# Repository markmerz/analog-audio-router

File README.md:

# analog-audio-router
Schematics and firmware for analog line level audio router/switchbox.

When You have some number of older audio gear then inputs count of power amplifier comes an issue. 
It would be nice to have some kind of switchbox for RCA inputs. There is not something like that in
the market, so i'm building one by myself. With blackjack!

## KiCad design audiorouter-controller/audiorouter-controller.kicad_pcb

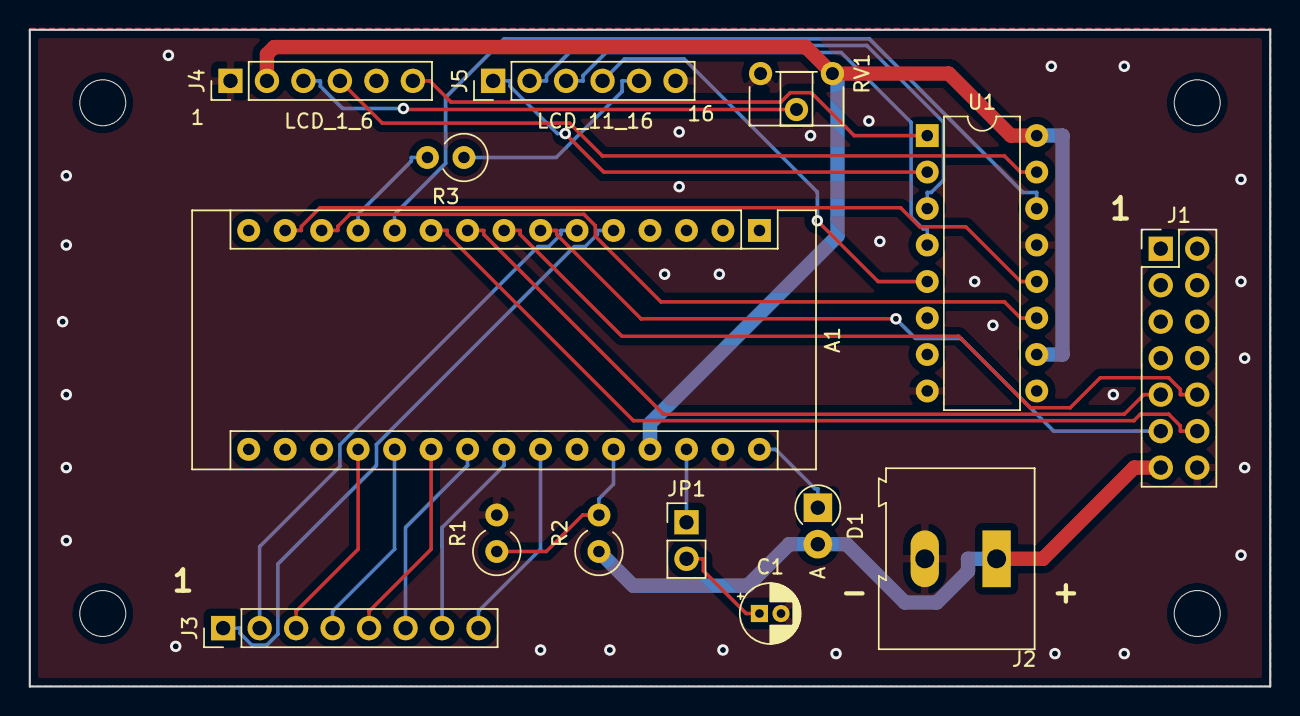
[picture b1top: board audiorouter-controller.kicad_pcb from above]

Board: 2 copper layers, 86.4 x 45.7 mm, 18 parts (0 on the bottom side), 31 nets.

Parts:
A1: Arduino_Nano_v3.x; Arduino_Nano
C1: 10u; CP_Radial_D4.0mm_P1.50mm
D1: N4007; D_T-1_P2.54mm_Vertical_AnodeUp
H1, H2, H3, H4: MountingHole; MountingHole_3.2mm_M3
J1: ToBoards; PinHeader_2x07_P2.54mm_Vertical
J2: PowerIn; TerminalBlock_Altech_AK300-2_P5.00mm
J3: AUX; PinHeader_1x08_P2.54mm_Vertical
J4: LCD_1_6; PinHeader_1x06_P2.54mm_Vertical
J5: LCD_11_16; PinHeader_1x06_P2.54mm_Vertical
JP1: progEnable; PinHeader_1x02_P2.54mm_Vertical
R1: 33k; R_Axial_DIN0309_L9.0mm_D3.2mm_P2.54mm_Vertical
R2: 47k; R_Axial_DIN0309_L9.0mm_D3.2mm_P2.54mm_Vertical
R3: 220; R_Axial_DIN0309_L9.0mm_D3.2mm_P2.54mm_Vertical
RV1: 10k; Potentiometer_ACP_CA6-H2,5_Horizontal
U1: 74HC595; DIP-16_W7.62mm

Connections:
+5V: A1.27, J4.2, RV1.1, U1.10, U1.16
AUX1: A1.5, J3.1
AUX2: A1.6, J3.2
AUX3: A1.19, J3.3
AUX4: A1.20, J3.4
AUX5: A1.21, J3.5
AUX6: A1.22, J3.6
AUX7: A1.23, J3.7
AUX8: A1.24, J3.8
GND: A1.29, C1.2, J1.14, J2.2, J4.1, J4.5, J5.6, R1.2, RV1.3, U1.8, U1.13
LCD_LED: A1.12, R3.2
LCD_RClock: A1.14, U1.12
LCD_SerialClock: A1.13, U1.11
LCD_SerialOut: A1.11, U1.14
unnamed: A1.28, JP1.1
unnamed: A1.30, D1.1
unnamed: C1.1, JP1.2
unnamed: J4.3, RV1.2
unnamed: J4.4, U1.15
unnamed: J4.6, U1.1
unnamed: J5.1, U1.2
unnamed: J5.2, U1.3
unnamed: J5.3, U1.4
unnamed: J5.4, U1.5
unnamed: J5.5, R3.1
OutputEnable: A1.10, J1.12
PowerIn: D1.2, J1.13, J2.1, R2.1
PowerMeasure: A1.26, R1.1, R2.2
RClock: A1.8, J1.10
SerialClock: A1.7, J1.11
SerialOut: A1.9, J1.9

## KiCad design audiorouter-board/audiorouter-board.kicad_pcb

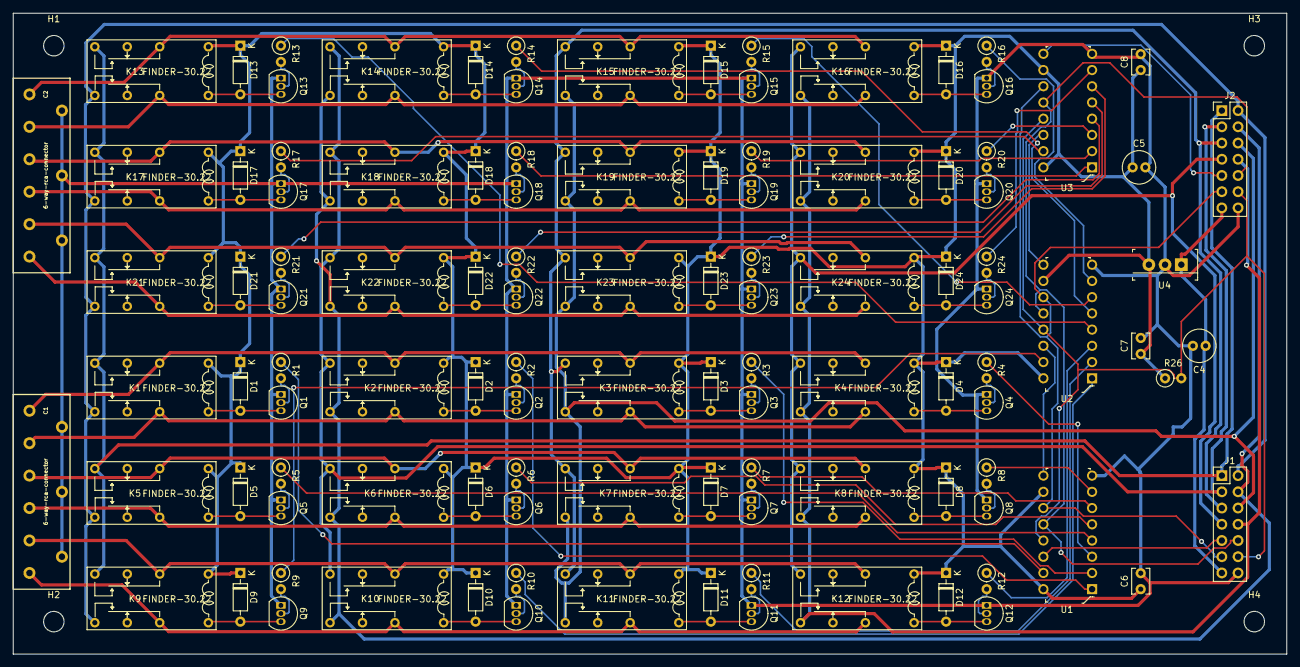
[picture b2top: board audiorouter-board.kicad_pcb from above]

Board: 2 copper layers, 199.4 x 100.3 mm, 114 parts (0 on the bottom side), 102 nets.

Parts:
C1, C2: 6-way-rca-connector; 6-way-rca-connector-on-edge
C4, C5: 10u; C_Radial_D5.0mm_H11.0mm_P2.00mm
C6, C7, C8: 10n; C_Disc_D3.8mm_W2.6mm_P2.50mm
D1, D2, D3, D4, D5, D6, D7, D8, D9, D10, D11, D12, D13, D14, D15, D16, D17, D18, D19, D20, D21, D22, D23, D24: 1N914; D_DO-35_SOD27_P7.62mm_Horizontal
H1, H2, H3, H4: MountingHole; MountingHole_3.2mm_M3
J1: Input_Ribbon_Connector; PinHeader_2x07_P2.54mm_Vertical
J2: Output_Ribbon_Connector; PinHeader_2x07_P2.54mm_Vertical
K1, K2, K3, K4, K5, K6, K7, K8, K9, K10, K11, K12, K13, K14, K15, K16, K17, K18, K19, K20, K21, K22, K23, K24: FINDER-30.22; RY12w-k_bigger_holes
Q1, Q2, Q3, Q4, Q5, Q6, Q7, Q8, Q9, Q10, Q11, Q12, Q13, Q14, Q15, Q16, Q17, Q18, Q19, Q20, Q21, Q22, Q23, Q24: PN2222A; TO-92_Inline
R1, R2, R3, R4, R5, R6, R7, R8, R9, R10, R11, R12, R13, R14, R15, R16, R17, R18, R19, R20, R21, R22, R23, R24: 1k; R_Axial_DIN0207_L6.3mm_D2.5mm_P2.54mm_Vertical
R26: 10k; R_Axial_DIN0207_L6.3mm_D2.5mm_P2.54mm_Vertical
U1, U2, U3: 74HC595; DIP-16_W7.62mm
U4: L7805; TO-220-3

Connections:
GND: C1.2, C1.5, C1.8, C2.2, C2.5, C2.8, C4.2, C5.2, C6.2, C7.2, C8.2, J1.14, J2.14, Q1.1, Q2.1, Q3.1, Q4.1, Q5.1, Q6.1, Q7.1, Q8.1, Q9.1, Q10.1, Q11.1, Q12.1, Q13.1, Q14.1, Q15.1, Q16.1, Q17.1, Q18.1, Q19.1, Q20.1, Q21.1, Q22.1, Q23.1, Q24.1, U1.8, U2.8, U3.8, U4.2
IN_1_B_1: R1.1, U1.15
IN_1_B_2: R2.1, U1.1
IN_1_B_3: R3.1, U1.2
IN_1_B_4: R4.1, U1.3
IN_2_B_1: R5.1, U1.4
IN_2_B_2: R6.1, U1.5
IN_2_B_3: R7.1, U1.6
IN_2_B_4: R8.1, U1.7
IN_3_B_1: R9.1, U2.15
IN_3_B_2: R10.1, U2.1
IN_3_B_3: R11.1, U2.2
IN_3_B_4: R12.1, U2.3
IN_4_B_1: R13.1, U2.4
IN_4_B_2: R14.1, U2.5
IN_4_B_3: R15.1, U2.6
IN_4_B_4: R16.1, U2.7
IN_5_B_1: R17.1, U3.15
IN_5_B_2: R18.1, U3.1
IN_5_B_3: R19.1, U3.2
IN_5_B_4: R20.1, U3.3
IN_6_B_1: R21.1, U3.4
IN_6_B_2: R22.1, U3.5
IN_6_B_3: R23.1, U3.6
IN_6_B_4: R24.1, U3.7
unnamed: C1.1, K1.21, K2.21, K3.21, K4.21
unnamed: C1.3, K1.11, K2.11, K3.11, K4.11
unnamed: C1.4, K5.21, K6.21, K7.21, K8.21
unnamed: C1.6, K5.11, K6.11, K7.11, K8.11
unnamed: C1.7, K9.21, K10.21, K11.21, K12.21
unnamed: C1.9, K9.11, K10.11, K11.11, K12.11
unnamed: C2.1, K13.21, K14.21, K15.21, K16.21
unnamed: C2.3, K13.11, K14.11, K15.11, K16.11
unnamed: C2.4, K17.21, K18.21, K19.21, K20.21
unnamed: C2.6, K17.11, K18.11, K19.11, K20.11
unnamed: C2.7, K21.21, K22.21, K23.21, K24.21
unnamed: C2.9, K21.11, K22.11, K23.11, K24.11
unnamed: D1.2, K1.A1, Q1.3
unnamed: D2.2, K2.A1, Q2.3
unnamed: D3.2, K3.A1, Q3.3
unnamed: D4.2, K4.A1, Q4.3
unnamed: D5.2, K5.A1, Q5.3
unnamed: D6.2, K6.A1, Q6.3
unnamed: D7.2, K7.A1, Q7.3
unnamed: D8.2, K8.A1, Q8.3
unnamed: D9.2, K9.A1, Q9.3
unnamed: D10.2, K10.A1, Q10.3
unnamed: D11.2, K11.A1, Q11.3
unnamed: D12.2, K12.A1, Q12.3
unnamed: D13.2, K13.A1, Q13.3
unnamed: D14.2, K14.A1, Q14.3
unnamed: D15.2, K15.A1, Q15.3
unnamed: D16.2, K16.A1, Q16.3
unnamed: D17.2, K17.A1, Q17.3
unnamed: D18.2, K18.A1, Q18.3
unnamed: D19.2, K19.A1, Q19.3
unnamed: D20.2, K20.A1, Q20.3
unnamed: D21.2, K21.A1, Q21.3
unnamed: D22.2, K22.A1, Q22.3
unnamed: D23.2, K23.A1, Q23.3
unnamed: D24.2, K24.A1, Q24.3
unnamed: Q1.2, R1.2
unnamed: Q2.2, R2.2
unnamed: Q3.2, R3.2
unnamed: Q4.2, R4.2
unnamed: Q5.2, R5.2
unnamed: Q6.2, R6.2
unnamed: Q7.2, R7.2
unnamed: Q8.2, R8.2
unnamed: Q9.2, R9.2
unnamed: Q10.2, R10.2
unnamed: Q11.2, R11.2
unnamed: Q12.2, R12.2
unnamed: Q13.2, R13.2
unnamed: Q14.2, R14.2
unnamed: Q15.2, R15.2
unnamed: Q16.2, R16.2
unnamed: Q17.2, R17.2
unnamed: Q18.2, R18.2
unnamed: Q19.2, R19.2
unnamed: Q20.2, R20.2
unnamed: Q21.2, R21.2
unnamed: Q22.2, R22.2
unnamed: Q23.2, R23.2
unnamed: Q24.2, R24.2
unnamed: U1.9, U2.14
unnamed: U2.9, U3.14
OutPutEnable: J1.12, J2.12, R26.2, U1.13, U2.13, U3.13
PowerIn: C4.1, J1.13, J2.13, U4.1
RClock: J1.10, J2.10, U1.12, U2.12, U3.12
SerialClock: J1.11, J2.11, U1.11, U2.11, U3.11
Serial_IN: J1.9, U1.14
Serial_OUT: J2.9, U3.9
VCC: C5.1, C6.1, C7.1, C8.1, D1.1, D2.1, D3.1, D4.1, D5.1, D6.1, D7.1, D8.1, D9.1, D10.1, D11.1, D12.1, D13.1, D14.1, D15.1, D16.1, D17.1, D18.1, D19.1, D20.1, D21.1, D22.1, D23.1, D24.1, K1.A2, K2.A2, K3.A2, K4.A2, K5.A2, K6.A2, K7.A2, K8.A2, K9.A2, K10.A2, K11.A2, K12.A2, K13.A2, K14.A2, K15.A2, K16.A2, K17.A2, K18.A2, K19.A2, K20.A2, K21.A2, K22.A2, K23.A2, K24.A2, R26.1, U1.10, U1.16, U2.10, U2.16, U3.10, U3.16, U4.3
bus_1_L: J1.1, J2.1, K1.24, K5.24, K9.24, K13.24, K17.24, K21.24
bus_1_R: J1.2, J2.2, K1.14, K5.14, K9.14, K13.14, K17.14, K21.14
bus_2_L: J1.3, J2.3, K2.24, K6.24, K10.24, K14.24, K18.24, K22.24
bus_2_R: J1.4, J2.4, K2.14, K6.14, K10.14, K14.14, K18.14, K22.14
bus_3_L: J1.5, J2.5, K3.24, K7.24, K11.24, K15.24, K19.24, K23.24
bus_3_R: J1.6, J2.6, K3.14, K7.14, K11.14, K15.14, K19.14, K23.14
bus_4_L: J1.7, J2.7, K4.24, K8.24, K12.24, K16.24, K20.24, K24.24
bus_4_R: J1.8, J2.8, K4.14, K8.14, K12.14, K16.14, K20.14, K24.14

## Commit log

2019-01-12 Add gitignore to repo
2019-01-12 Readme
2019-01-12 pics
2019-03-05 Changes and bodges.
2020-03-16 Turned out that time delay circut for 595 output enable pins was bad idea in practice. I reworked my device by removing timed pull-down circuit components while leaving pull-up in place. Added wires 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
    Rewrote controller board arduino software for output enable logic.
    Fixed bugs that caused parasitic powering of daughter boards via
    595 data pins. Worked around noise induced false triggering by
    overwriting correct state to 595 cascade every second. Added
    software logic for drawn current limiting.
2020-04-15 Bugfixes for power management.
2020-04-15 Next revison: hardware support for lcd character display and matrix keyboards. Should be generic enough to connect something else when ideas changes. Last revision was for home-made pcb. This revisio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
2020-05-01 Bummer, some of the ground plane was left unconnected. I bodged with wire and won't order new pcbs. Fixing in repo regardless.
